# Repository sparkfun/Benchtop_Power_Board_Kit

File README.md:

Benchtop Power Board Kit
========================

[*Benchtop Power Board Kit (KIT-09774)*](https://www.sparkfun.com/products/9774)

The benchtop power board kit was created to provide quick access to the typical voltages needed when 
developing physical computing projects. The kit provides access to 3.3V, 5V, 12V and -12V. After assembling the kit you'll have access to four different voltages (3.3V, 5V, 12V and -12V) each with their own replaceable 5A fuse

Repository Contents
-------------------
* **/Hardware** - All Eagle design files (.brd, .sch)

Documentation
-------------------
* **[Hookup Guide](https://learn.sparkfun.com/tutorials/benchtop-power-board-kit-hookup-guide)**

License Information
-------------------
The hardware is released under [Creative Commons ShareAlike 4.0 International](https://creativecommons.org/licenses/by-sa/4.0/).

Distributed as-is; no warranty is given.

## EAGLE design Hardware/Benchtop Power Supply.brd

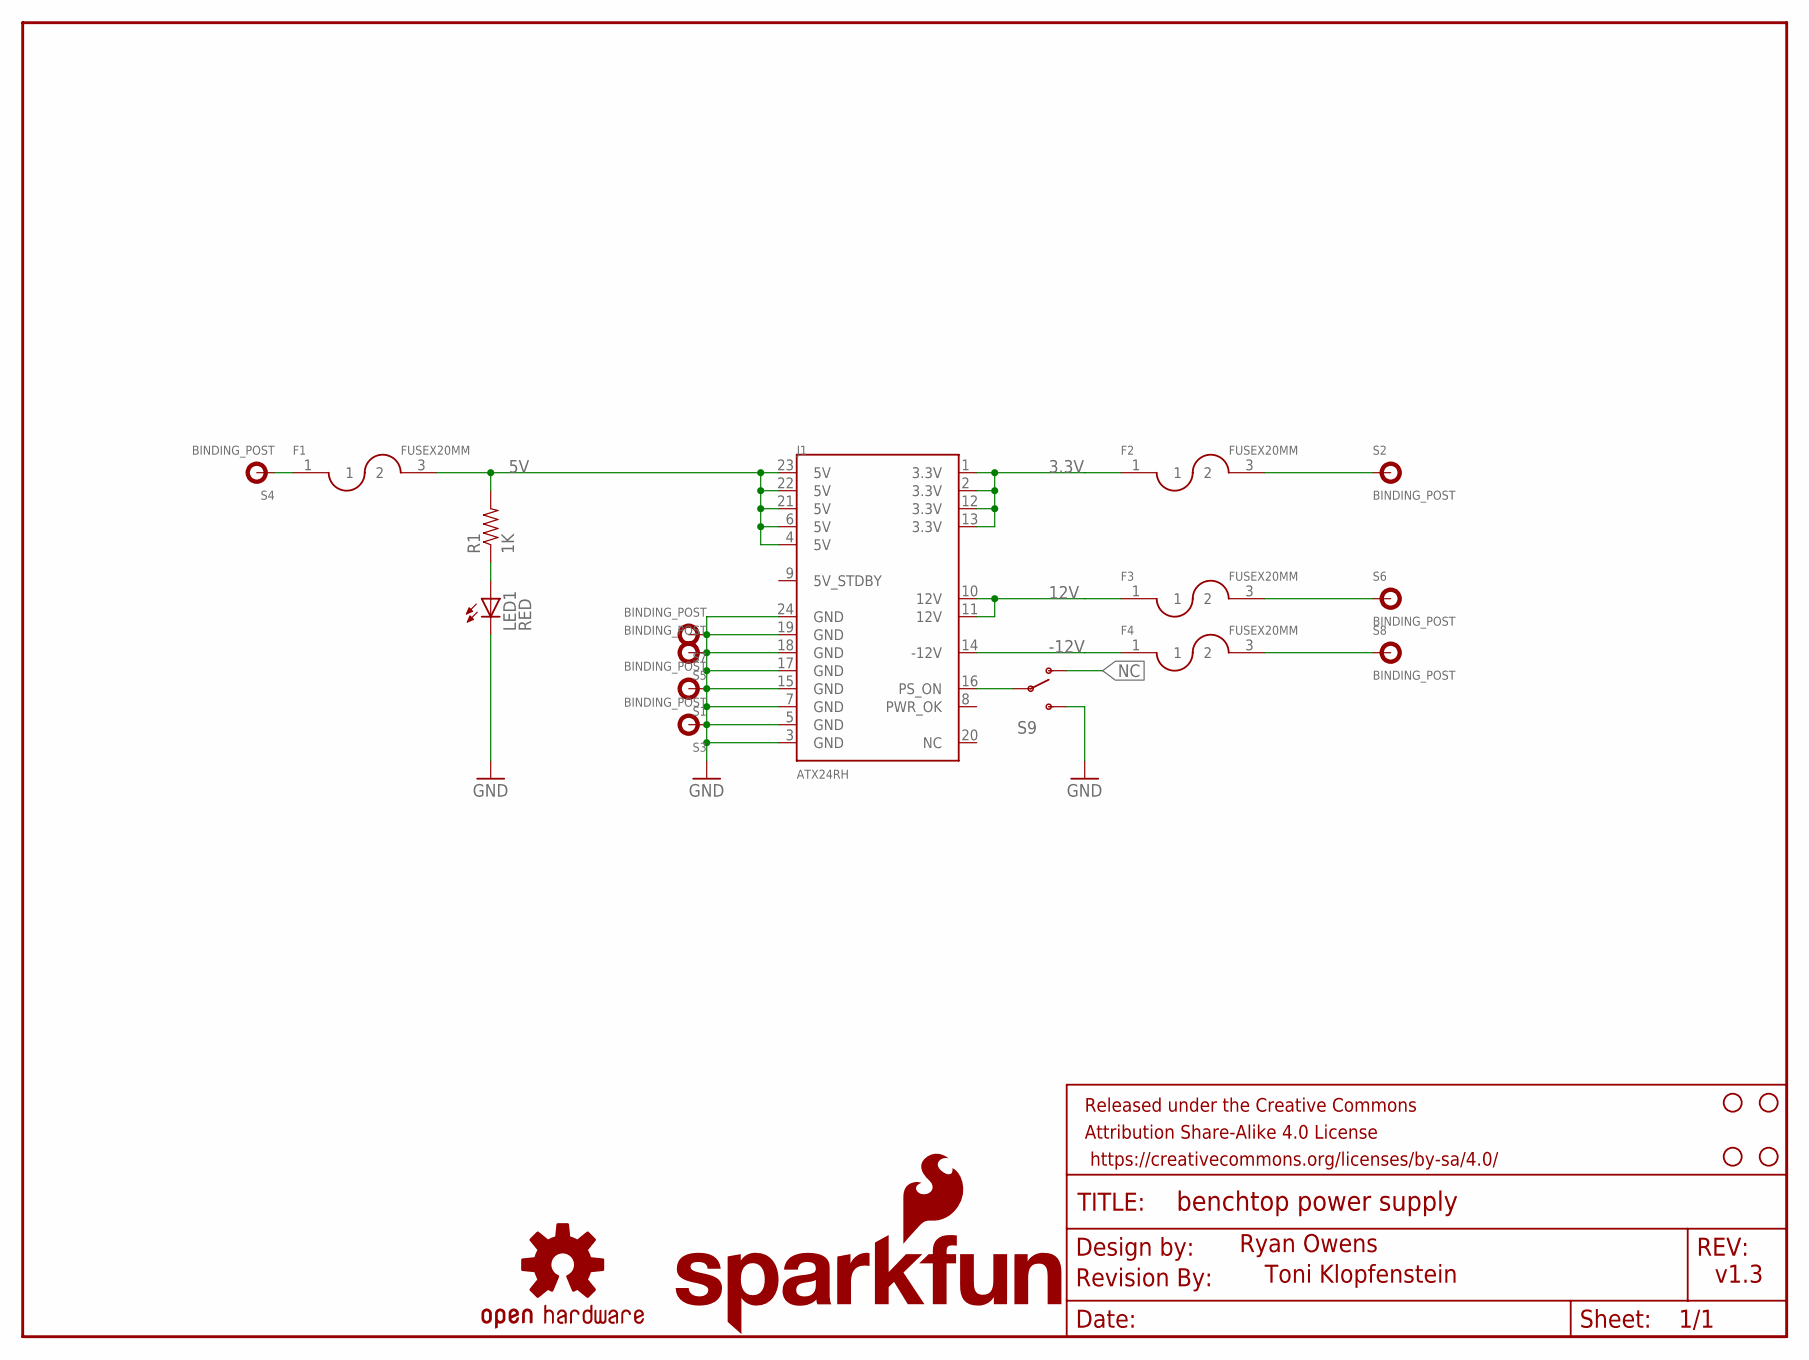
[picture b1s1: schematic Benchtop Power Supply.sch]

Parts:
F1, F2, F3, F4: FUSEX20MM; FUSE_5MM
FRAME1: FRAME-LETTER; CREATIVE_COMMONS
J1: ATX24RH; ATX24_RIGHT_ANGLE
JP1: SFE_LOGO_NAME_FLAME.3_INCH; SFE_LOGO_NAME_FLAME_.3
JP2, JP3, JP4, JP5: STAND-OFF
LED1: RED; LED5MM
LOGO1: OSHW-LOGOL; OSHW-LOGO-L
R1: 1K; AXIAL-0.3
S1, S2, S3, S4, S5, S6, S7, S8: BINDING_POST
S9: SWITCH-SPDTKIT; SWITCH-SPDT_KIT
U$1: REVISION

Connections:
3.3V: F2.1, J1.1 (3.3V), J1.2 (3.3V), J1.12 (3.3V), J1.13 (3.3V)
3.3V_P: F2.3 (2), S2.P$1
5V: F1.3 (2), J1.4 (5V), J1.6 (5V), J1.21 (5V), J1.22 (5V), J1.23 (5V), R1.P$2 (2)
5V_P: F1.1, S4.P$1
12V: F3.1, J1.10 (12V), J1.11 (12V)
12V_P: F3.3 (2), S6.P$1
-12V: F4.1, J1.14 (-12V)
-12V_P: F4.3 (2), S8.P$1
GND: J1.3 (GND), J1.5 (GND), J1.7 (GND), J1.15 (GND), J1.17 (GND), J1.18 (GND), J1.19 (GND), J1.24 (GND), LED1.K (C), S1.P$1, S3.P$1, S5.P$1, S7.P$1, S9.3 (S)
unnamed: LED1.A, R1.P$1 (1)
unnamed: J1.16 (PS_ON), S9.2
NC: S9.1 (O)

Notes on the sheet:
Ryan Owens
Toni Klopfenstein
v1.3

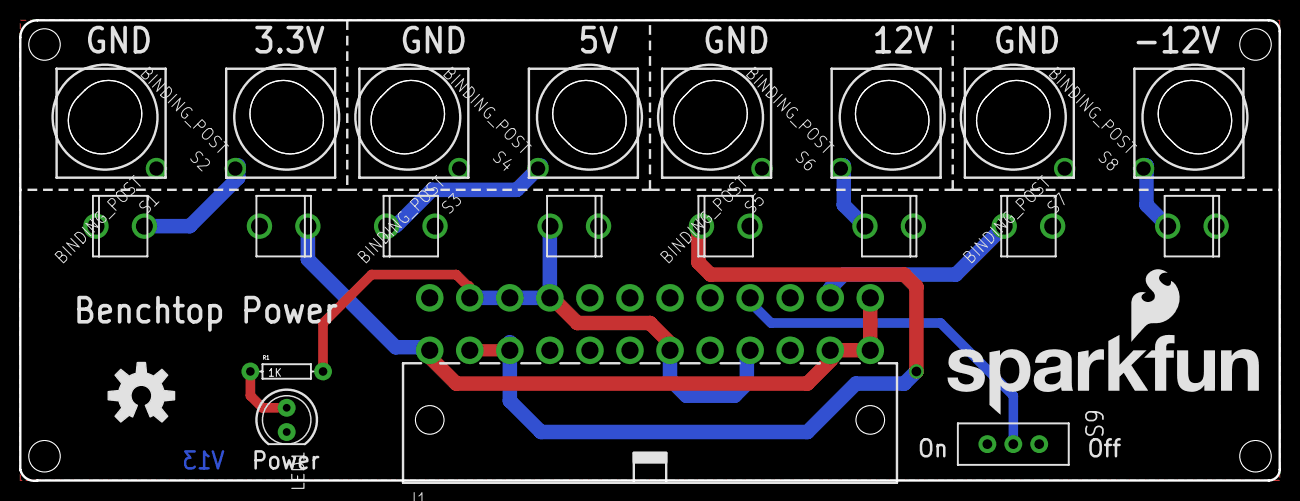
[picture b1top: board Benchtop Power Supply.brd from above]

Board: 2 copper layers, 132.1 x 48.3 mm, 24 parts (0 on the bottom side), 11 nets.

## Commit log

2014-04-10 Initial hardware file commit
2014-04-10 Updating file name
2014-04-11 Midway hardware changes
2014-04-11 Files changed for V13- ready for review
2014-04-15 Adding rounded corners, square binding post holes, increased traces to 60 mil
2014-05-20 Fixing drill holes for mounting posts
2014-07-14 Updating to new binding post footprint
2014-07-15 Fixing review commentaries

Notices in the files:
parts and their libraries:
SparkFun-Connectors: Licensing: Creative Commons ShareAlike 4.0 International - https://creativecommons.org/licenses/by-sa/4.0
SparkFun-Aesthetics: Released under the Creative Commons Attribution Share-Alike 4.0 License
SparkFun-Aesthetics: Released under the Creative Commons
